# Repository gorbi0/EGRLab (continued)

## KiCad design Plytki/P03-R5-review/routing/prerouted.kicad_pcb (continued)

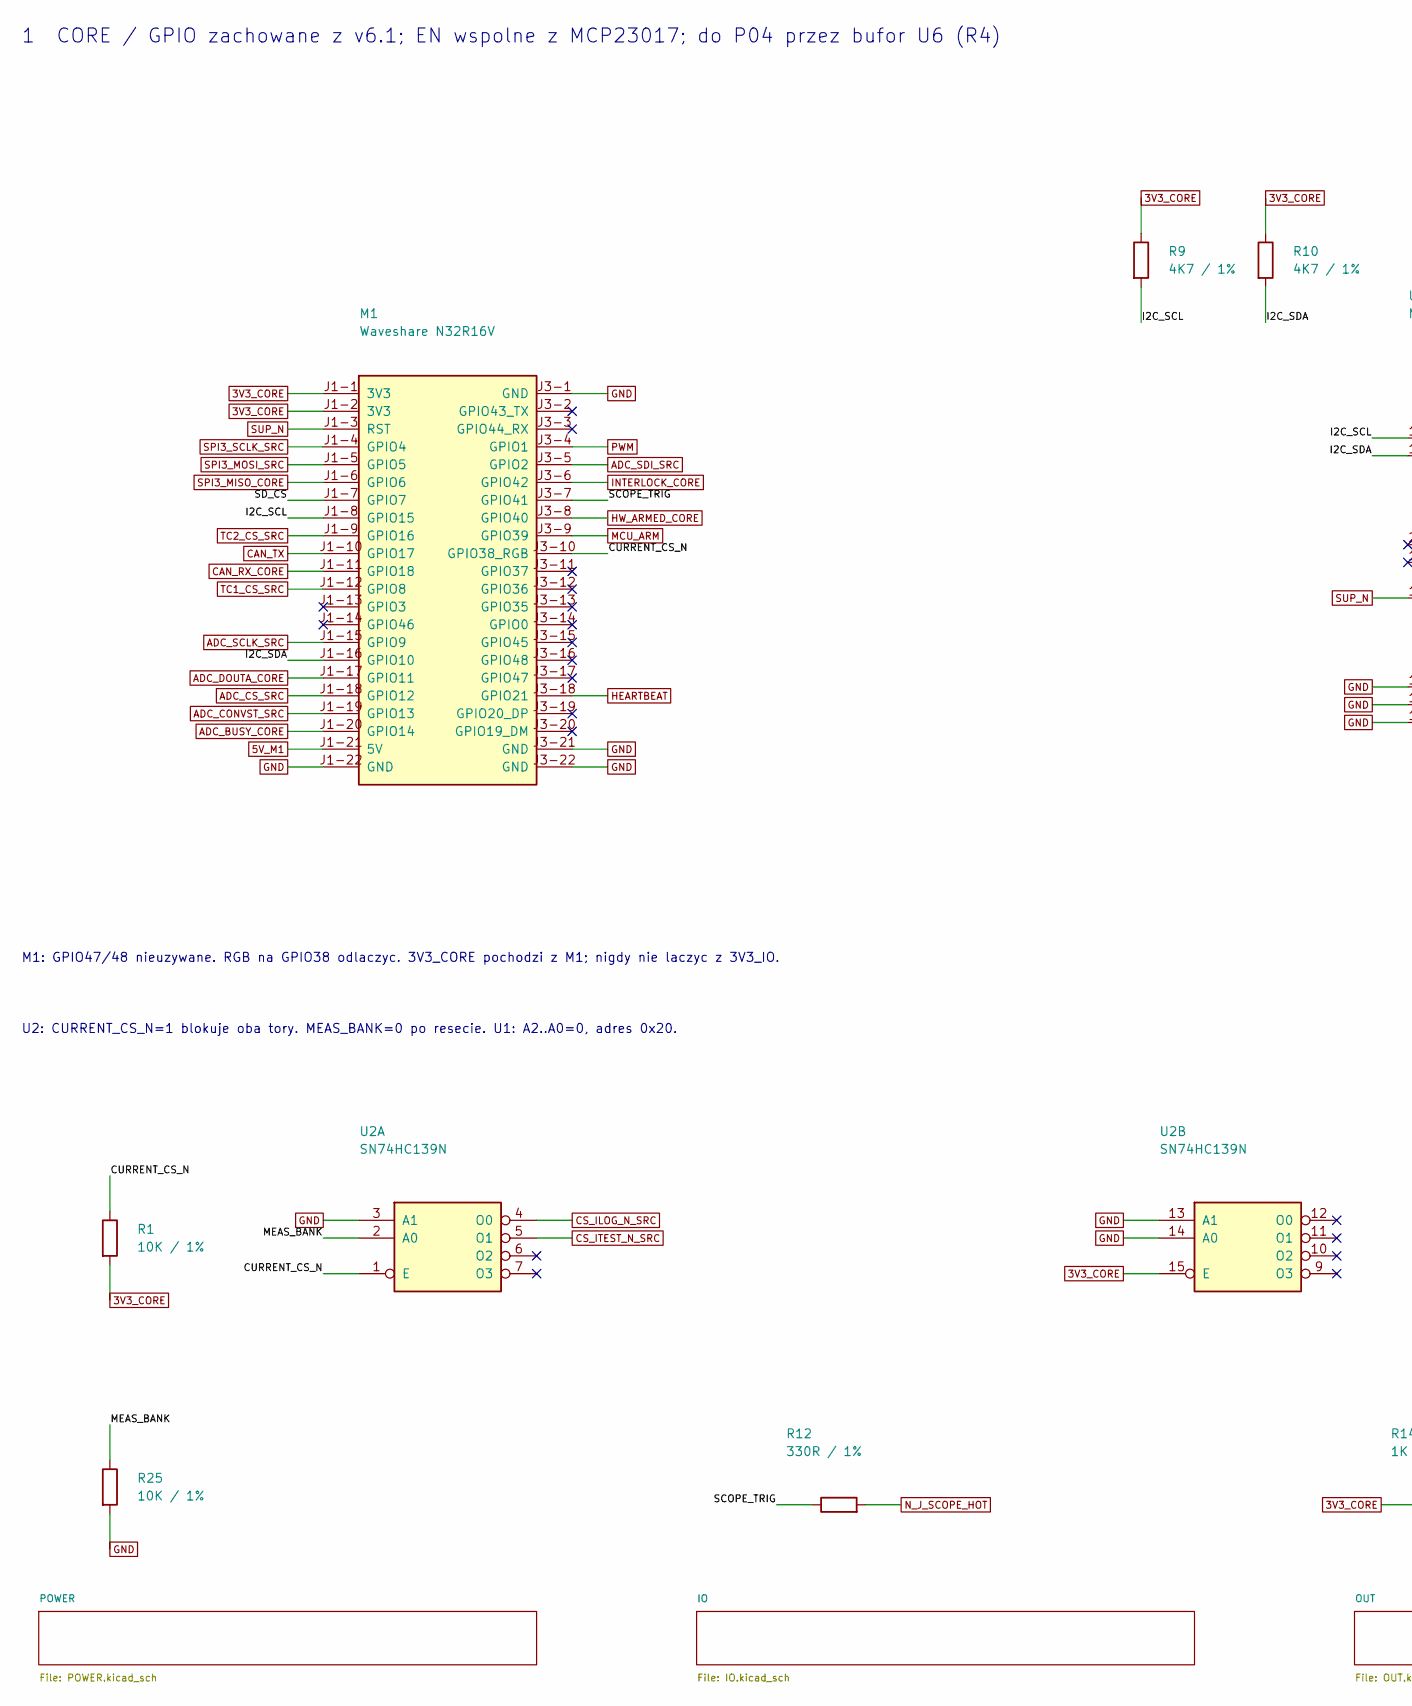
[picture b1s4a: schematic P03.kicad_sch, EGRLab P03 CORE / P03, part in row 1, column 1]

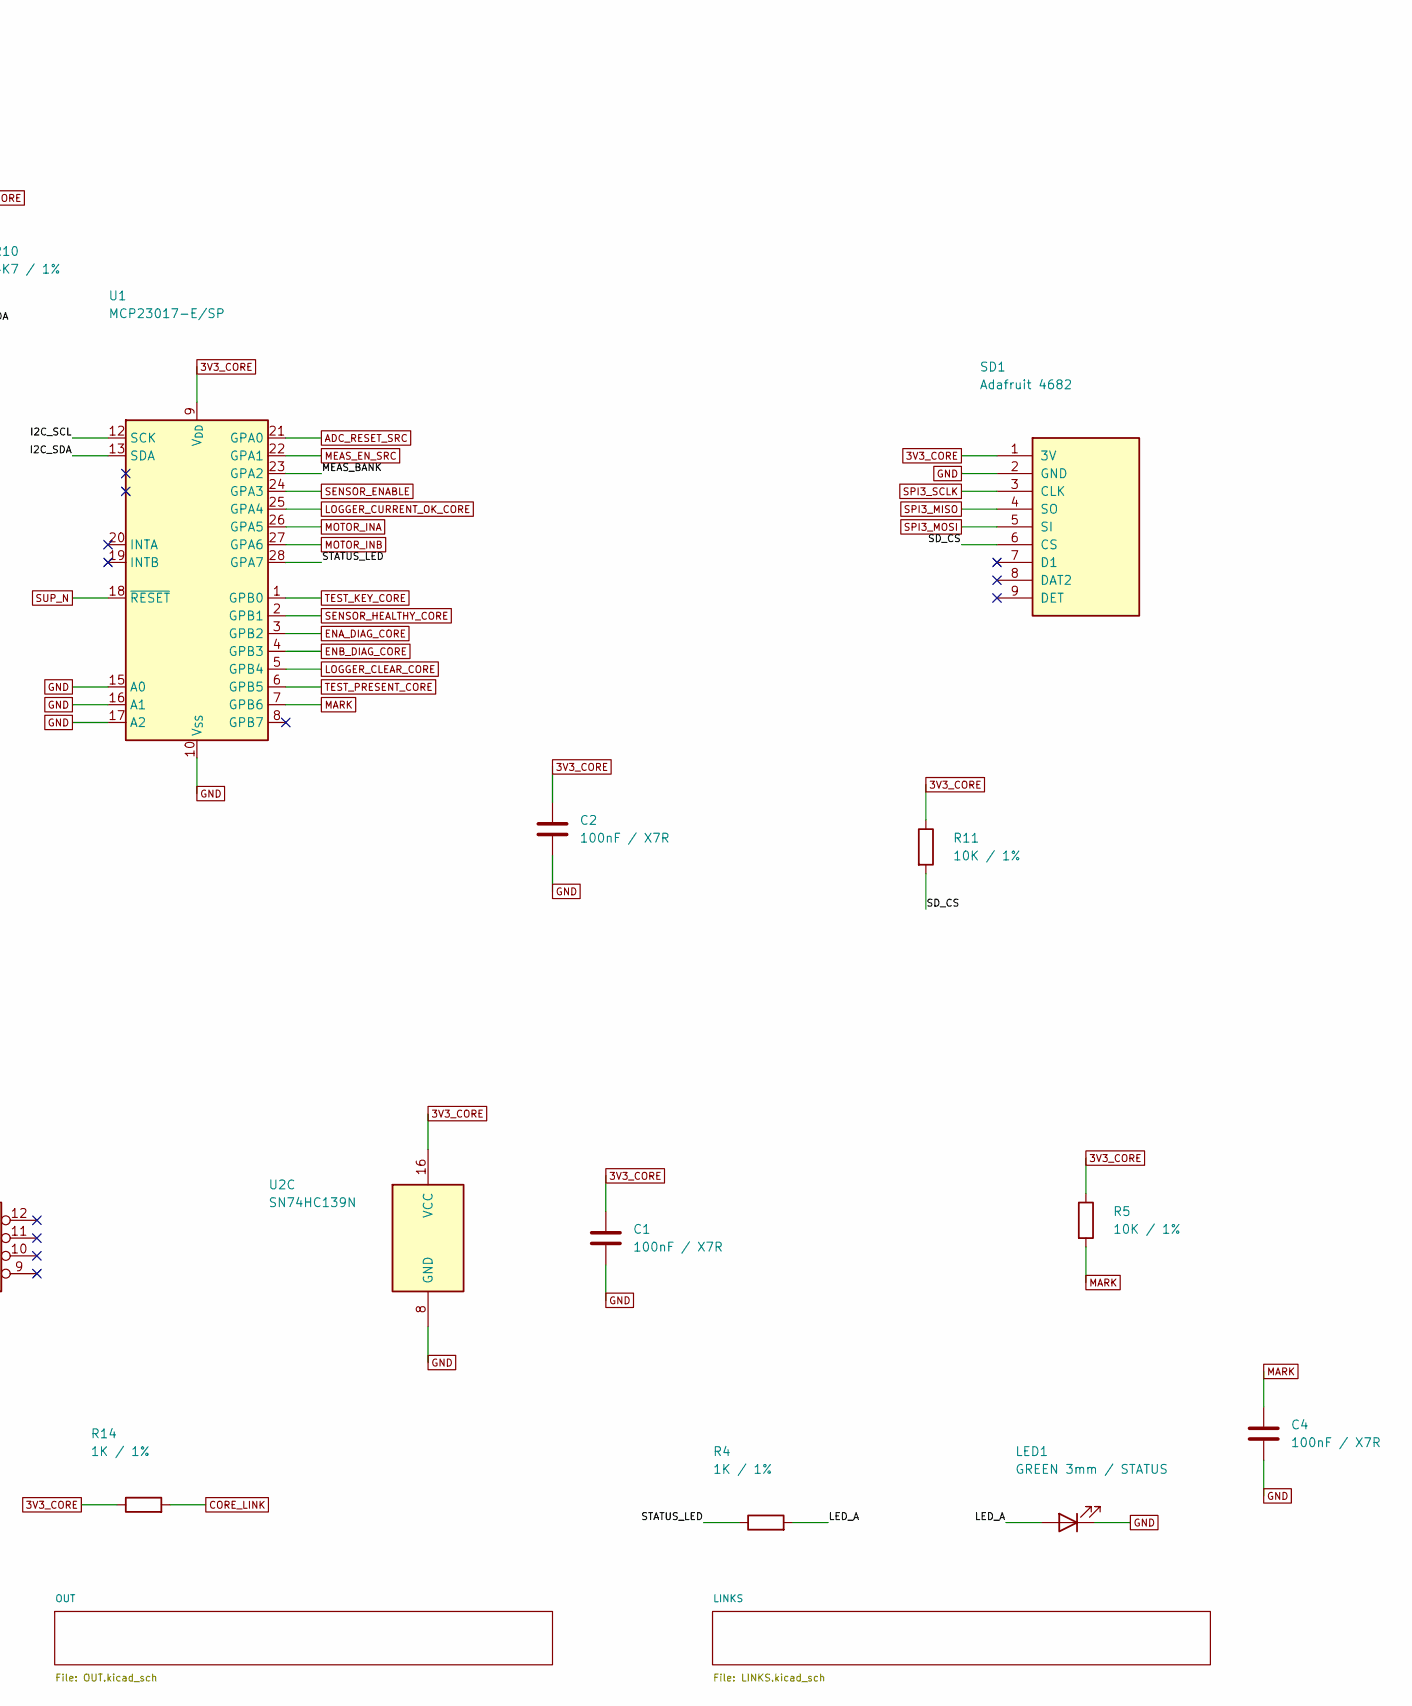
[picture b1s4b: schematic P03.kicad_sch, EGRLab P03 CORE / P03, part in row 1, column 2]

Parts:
C1, C2, C4: 100nF / X7R; C_Vishay_K15_H5_P5; MPN K104K15X7RF53H5
LED1: GREEN 3mm / STATUS; LED_D3.0mm; MPN L-934GD
M1: Waveshare N32R16V; Waveshare_ESP32-S3-DEV-KIT_2x22_W22.86; MPN owned (Waveshare ESP32-S3-DEV-KIT-N32R1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
R1, R5, R11, R25: 10K / 1%; R_Axial_DIN0207_L6.3mm_D2.5mm_P10.16mm_Horizontal; MPN MF0207FTE-10K
R4, R14: 1K / 1%; R_Axial_DIN0207_L6.3mm_D2.5mm_P10.16mm_Horizontal; MPN MF0207FTE-1K
R9, R10: 4K7 / 1%; R_Axial_DIN0207_L6.3mm_D2.5mm_P10.16mm_Horizontal; MPN MF0207FTE-4K7
R12: 330R / 1%; R_Axial_DIN0207_L6.3mm_D2.5mm_P10.16mm_Horizontal; MPN MF0207FTE-330R
SD1: Adafruit 4682; Adafruit_4682_microSD_1x09; MPN Adafruit 4682 on a 1x9 female header + 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
U1: MCP23017-E/SP; DIP-28_W7.62mm; MPN MCP23017-E/SP
U2: SN74HC139N; DIP-16_W7.62mm; MPN SN74HC139N

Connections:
3V3_CORE: C1.1, C2.1, M1.J1-1 (3V3), M1.J1-2 (3V3), R1.2, R5.1, R9.1, R10.1, R11.1, R14.1, SD1.1 (3V), U1.9 (V_{DD}), U2.15 (E), U2.16 (VCC); also elsewhere on the board
5V_M1: M1.J1-21 (5V); also elsewhere on the board
/CURRENT_CS_N: M1.J3-10 (GPIO38_RGB), R1.1, U2.1 (E)
/I2C_SCL: M1.J1-8 (GPIO15), R9.2, U1.12 (SCK)
/I2C_SDA: M1.J1-16 (GPIO10), R10.2, U1.13 (SDA)
/LED_A: LED1.2 (A), R4.2
/MEAS_BANK: R25.1, U1.23 (GPA2), U2.2 (A0)
/SCOPE_TRIG: M1.J3-7 (GPIO41), R12.1
/SD_CS: M1.J1-7 (GPIO7), R11.2, SD1.6 (CS)
/STATUS_LED: R4.1, U1.28 (GPA7)
ADC_BUSY_CORE: M1.J1-20 (GPIO14); also elsewhere on the board
ADC_CONVST_SRC: M1.J1-19 (GPIO13); also elsewhere on the board
ADC_CS_SRC: M1.J1-18 (GPIO12); also elsewhere on the board
ADC_DOUTA_CORE: M1.J1-17 (GPIO11); also elsewhere on the board
ADC_RESET_SRC: U1.21 (GPA0); also elsewhere on the board
ADC_SCLK_SRC: M1.J1-15 (GPIO9); also elsewhere on the board
ADC_SDI_SRC: M1.J3-5 (GPIO2); also elsewhere on the board
CAN_RX_CORE: M1.J1-11 (GPIO18); also elsewhere on the board
CAN_TX: M1.J1-10 (GPIO17); also elsewhere on the board
CORE_LINK: R14.2; also elsewhere on the board
CS_ILOG_N_SRC: U2.4 (O0); also elsewhere on the board
CS_ITEST_N_SRC: U2.5 (O1); also elsewhere on the board
ENA_DIAG_CORE: U1.3 (GPB2); also elsewhere on the board
ENB_DIAG_CORE: U1.4 (GPB3); also elsewhere on the board
GND: C1.2, C2.2, C4.2, LED1.1 (K), M1.J1-22 (GND), M1.J3-1 (GND), M1.J3-21 (GND), M1.J3-22 (GND), R25.2, SD1.2 (GND), U1.10 (V_{SS}), U1.15 (A0), U1.16 (A1), U1.17 (A2), U2.3 (A1), U2.8 (GND), U2.13 (A1), U2.14 (A0); also elsewhere on the board
HEARTBEAT: M1.J3-18 (GPIO21); also elsewhere on the board
HW_ARMED_CORE: M1.J3-8 (GPIO40); also elsewhere on the board
INTERLOCK_CORE: M1.J3-6 (GPIO42); also elsewhere on the board
LOGGER_CLEAR_CORE: U1.5 (GPB4); also elsewhere on the board
LOGGER_CURRENT_OK_CORE: U1.25 (GPA4); also elsewhere on the board
MARK: C4.1, R5.2, U1.7 (GPB6); also elsewhere on the board
MCU_ARM: M1.J3-9 (GPIO39); also elsewhere on the board
MEAS_EN_SRC: U1.22 (GPA1); also elsewhere on the board
MOTOR_INA: U1.26 (GPA5); also elsewhere on the board
MOTOR_INB: U1.27 (GPA6); also elsewhere on the board
N_J_SCOPE_HOT: R12.2; also elsewhere on the board
PWM: M1.J3-4 (GPIO1); also elsewhere on the board
SENSOR_ENABLE: U1.24 (GPA3); also elsewhere on the board
SENSOR_HEALTHY_CORE: U1.2 (GPB1); also elsewhere on the board
SPI3_MISO: SD1.4 (SO); also elsewhere on the board
SPI3_MISO_CORE: M1.J1-6 (GPIO6); also elsewhere on the board
SPI3_MOSI: SD1.5 (SI); also elsewhere on the board
SPI3_MOSI_SRC: M1.J1-5 (GPIO5); also elsewhere on the board
SPI3_SCLK: SD1.3 (CLK); also elsewhere on the board
SPI3_SCLK_SRC: M1.J1-4 (GPIO4); also elsewhere on the board
SUP_N: M1.J1-3 (RST), U1.18 (~RESET); also elsewhere on the board
TC1_CS_SRC: M1.J1-12 (GPIO8); also elsewhere on the board
TC2_CS_SRC: M1.J1-9 (GPIO16); also elsewhere on the board
TEST_KEY_CORE: U1.1 (GPB0); also elsewhere on the board
TEST_PRESENT_CORE: U1.6 (GPB5); also elsewhere on the board

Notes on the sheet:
1 CORE / GPIO zachowane z v6.1; EN wspolne z MCP23017; do P04 przez bufor U6 (R4)
M1: GPIO47/48 nieuzywane. RGB na GPIO38 odlaczyc. 3V3_CORE pochodzi z M1; nigdy nie laczyc z 3V3_IO.
U2: CURRENT_CS_N=1 blokuje oba tory. MEAS_BANK=0 po resecie. U1: A2..A0=0, adres 0x20.

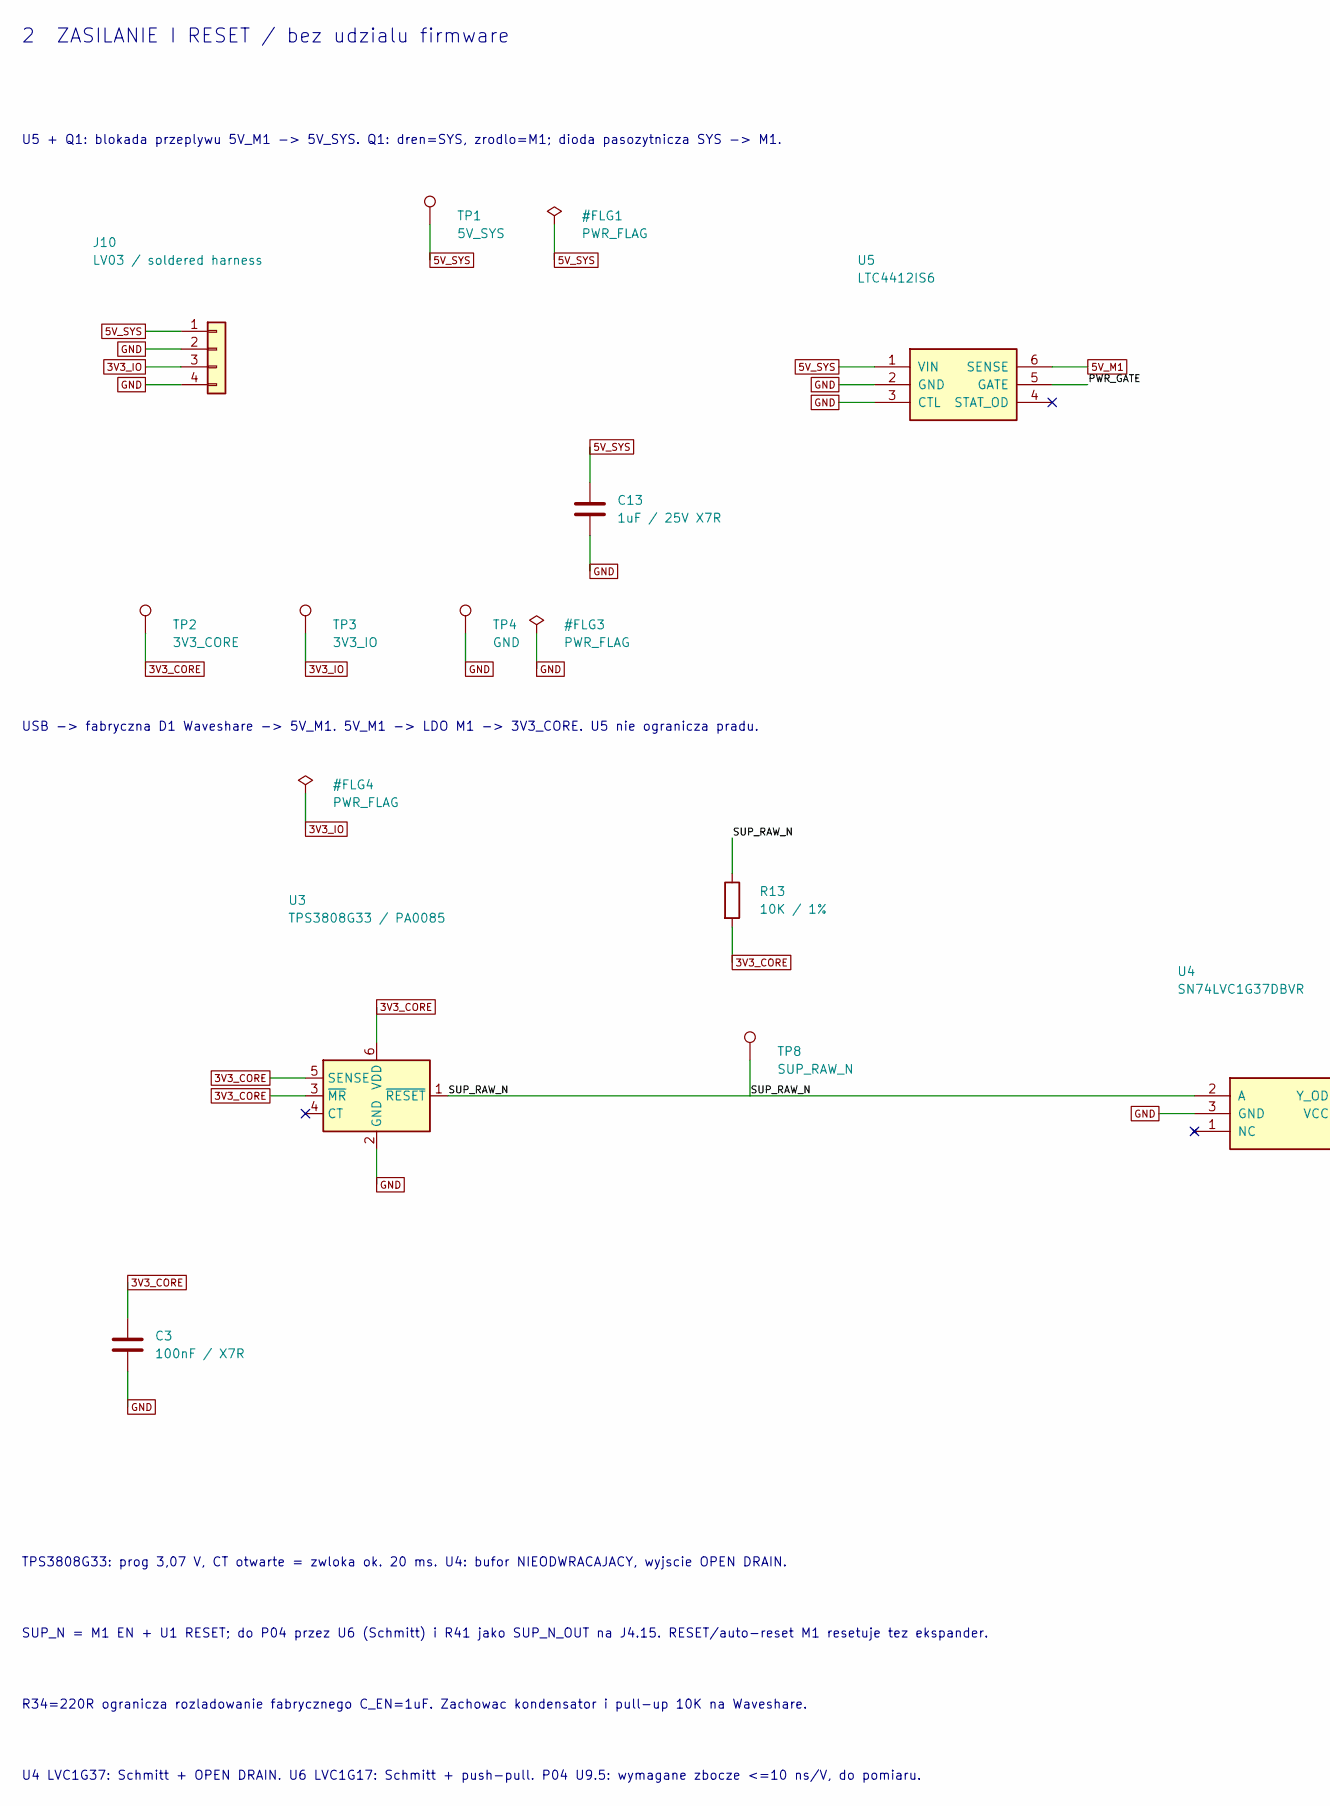
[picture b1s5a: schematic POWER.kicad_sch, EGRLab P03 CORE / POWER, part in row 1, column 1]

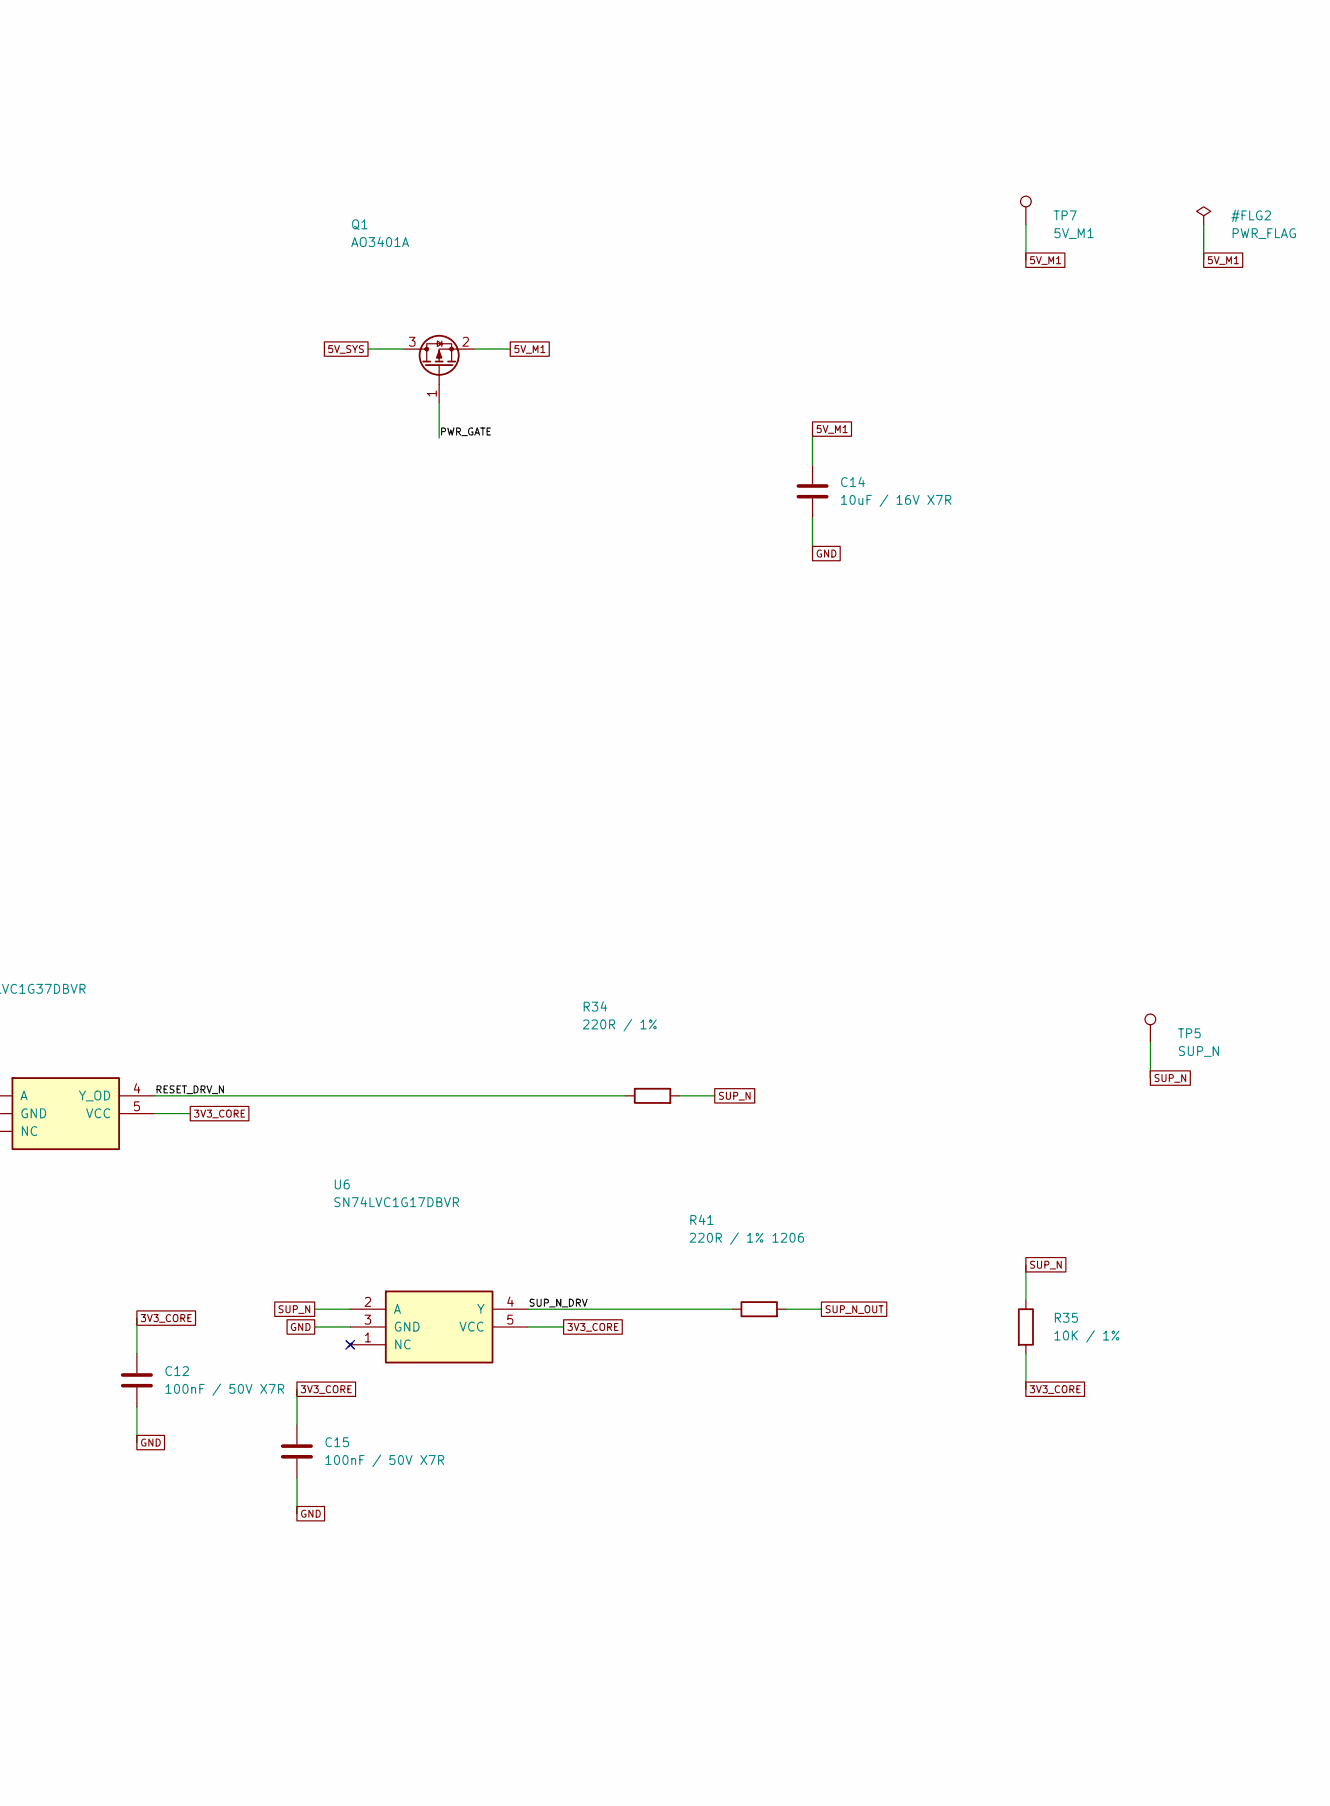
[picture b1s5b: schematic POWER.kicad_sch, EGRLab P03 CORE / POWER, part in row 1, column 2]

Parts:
C3: 100nF / X7R; C_Vishay_K15_H5_P5; MPN K104K15X7RF53H5
C12, C15: 100nF / 50V X7R; C_1206_3216Metric_Pad1.33x1.80mm_HandSolder; MPN GRM31CR71H104KA01L
C13: 1uF / 25V X7R; C_1206_3216Metric_Pad1.33x1.80mm_HandSolder; MPN GRM31CR71E105KA12L
C14: 10uF / 16V X7R; C_1206_3216Metric_Pad1.33x1.80mm_HandSolder; MPN GRM31CR71C106KA12L
J10: LV03 / soldered harness; Pigtail_LV_4xAWG22_P3.81; MPN PCB termination; H_LV03 from P02 J3
Q1: AO3401A; SOT-23; MPN AO3401A
R13, R35: 10K / 1%; R_Axial_DIN0207_L6.3mm_D2.5mm_P10.16mm_Horizontal; MPN MF0207FTE-10K
R34: 220R / 1%; R_Axial_DIN0207_L6.3mm_D2.5mm_P10.16mm_Horizontal; MPN MF0207FTE-220R
R41: 220R / 1% 1206; R_1206_3216Metric_Pad1.30x1.75mm_HandSolder; MPN RC1206FR-07220RL
TP1: 5V_SYS; TestPad_1; MPN PCB test pad
TP2: 3V3_CORE; TestPad_1; MPN PCB test pad
TP3: 3V3_IO; TestPad_1; MPN PCB test pad
TP4: GND; TestPad_1; MPN PCB test pad
TP5: SUP_N; TestPad_1; MPN PCB test pad
TP7: 5V_M1; TestPad_1; MPN PCB test pad
TP8: SUP_RAW_N; TestPad_1; MPN PCB test pad
U3: TPS3808G33 / PA0085; Adapter_SOT23-6_DIP6_W15.24_ChipQuik_PA0085; MPN TPS3808G33DBVR on Chip Quik PA0085
U4: SN74LVC1G37DBVR; SOT-23-5; MPN SN74LVC1G37DBVR
U5: LTC4412IS6; SOT-23-6; MPN LTC4412IS6#TRPBF
U6: SN74LVC1G17DBVR; SOT-23-5; MPN SN74LVC1G17DBVR

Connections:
3V3_CORE: C3.1, C12.1, C15.1, R13.2, R35.2, TP2.1, U3.3 (~MR), U3.5 (SENSE), U3.6 (VDD), U4.5 (VCC), U6.5 (VCC); also elsewhere on the board
3V3_IO: J10.3, TP3.1; also elsewhere on the board
5V_M1: C14.1, Q1.2 (S), TP7.1, U5.6 (SENSE); also elsewhere on the board
5V_SYS: C13.1, J10.1, Q1.3 (D), TP1.1, U5.1 (VIN)
/POWER/PWR_GATE: Q1.1 (G), U5.5 (GATE)
/POWER/RESET_DRV_N: R34.1, U4.4 (Y_OD)
/POWER/SUP_N_DRV: R41.1, U6.4 (Y)
/POWER/SUP_RAW_N: R13.1, TP8.1, U3.1 (~RESET), U4.2 (A)
GND: C3.2, C12.2, C13.2, C14.2, C15.2, J10.2, J10.4, TP4.1, U3.2 (GND), U4.3 (GND), U5.2 (GND), U5.3 (CTL), U6.3 (GND); also elsewhere on the board
SUP_N: R34.2, R35.1, TP5.1, U6.2 (A); also elsewhere on the board
SUP_N_OUT: R41.2; also elsewhere on the board

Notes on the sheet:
2 ZASILANIE I RESET / bez udzialu firmware
U5 + Q1: blokada przeplywu 5V_M1 -> 5V_SYS. Q1: dren=SYS, zrodlo=M1; dioda pasozytnicza SYS -> M1.
USB -> fabryczna D1 Waveshare -> 5V_M1. 5V_M1 -> LDO M1 -> 3V3_CORE. U5 nie ogranicza pradu.
TPS3808G33: prog 3,07 V, CT otwarte = zwloka ok. 20 ms. U4: bufor NIEODWRACAJACY, wyjscie OPEN DRAIN.
SUP_N = M1 EN + U1 RESET; do P04 przez U6 (Schmitt) i R41 jako SUP_N_OUT na J4.15. RESET/auto-reset M1 resetuje tez ekspander.
R34=220R ogranicza rozladowanie fabrycznego C_EN=1uF. Zachowac kondensator i pull-up 10K na Waveshare.
U4 LVC1G37: Schmitt + OPEN DRAIN. U6 LVC1G17: Schmitt + push-pull. P04 U9.5: wymagane zbocze <=10 ns/V, do pomiaru.

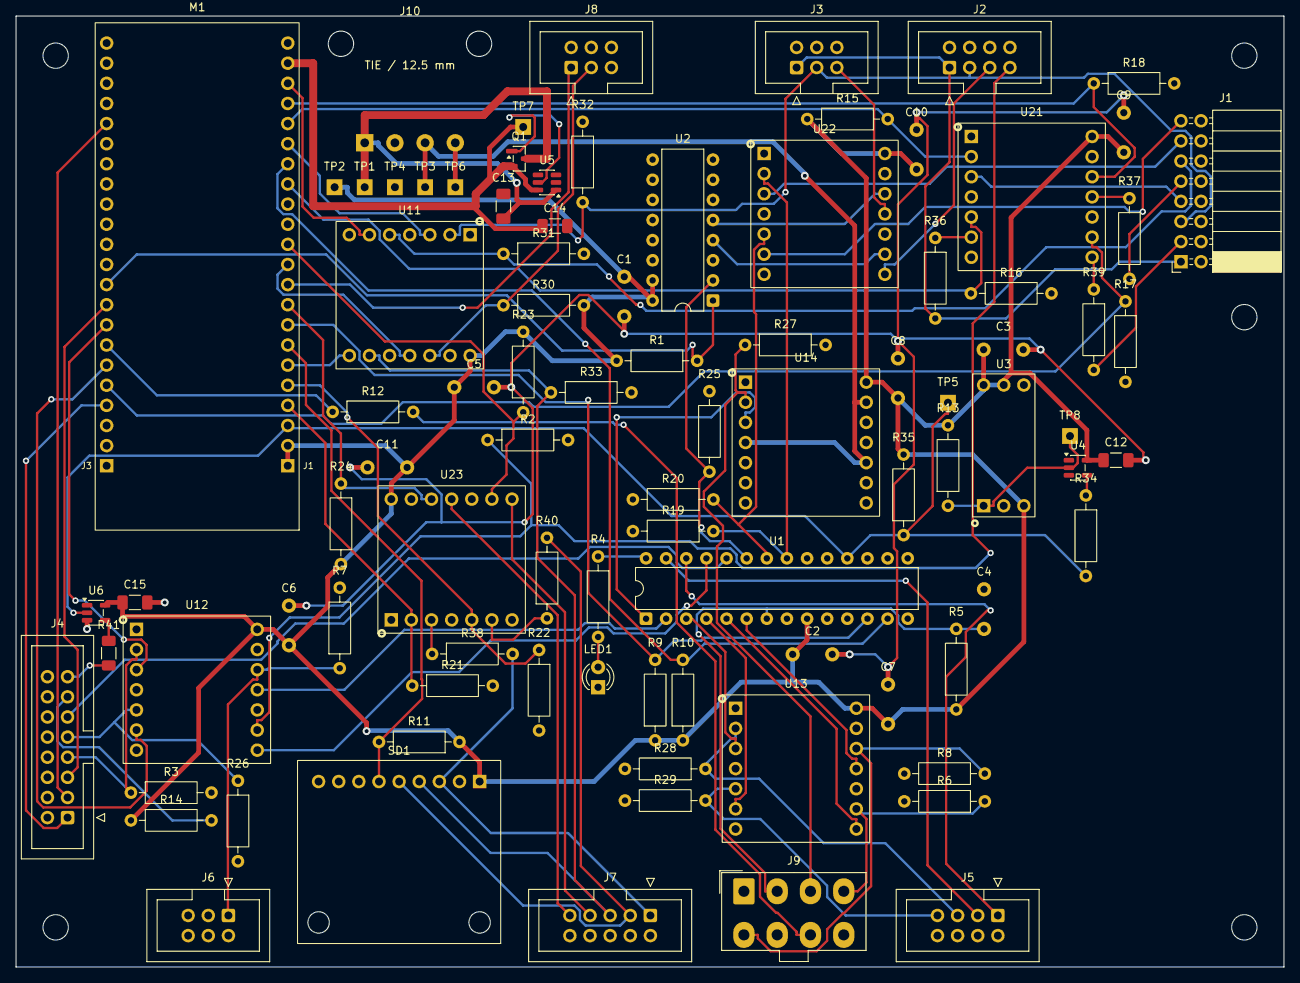
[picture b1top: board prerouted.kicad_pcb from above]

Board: 2 copper layers, 160.0 x 120.0 mm, 96 parts (0 on the bottom side), 84 nets.

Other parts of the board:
H1, H2, H3, H4, H5: M3 NPTH

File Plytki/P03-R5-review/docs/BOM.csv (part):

ref;source_ref;display;mpn;qty;footprint;url;note
M1;M1;Waveshare N32R16V;owned (Waveshare ESP32-S3-DEV-KIT-N32R16V) on 2x 1x22 female headers;1;P03:Waveshare_ESP32-S3-DEV-KIT_2x22_W22.86;https://docs.waveshare.com/ESP32-S3-DEV-KIT-N8R8;"Rows 22.86 mm (measured). GPIO numbers are the v6.1 contract. Remove the on-board RGB LED on GPIO38 (v6.1). GPIO47/48 1.8 V: unused. 3V3 = 3V3_CORE; never tie to 3V3_IO."
SD1;SD1;Adafruit 4682;Adafruit 4682 on a 1x9 female header + 2x M2.5 spacer;1;P03:Adafruit_4682_microSD_1x09;https://www.adafruit.com/product/4682;User decision 25.09: Adafruit 4682 (3 V only, no regulator/level shifter). SO = card out (MISO), SI = card in (MOSI). D1, DAT2, DET unused.
U1;U17;MCP23017-E/SP;MCP23017-E/SP;1;Package_DIP:DIP-28_W7.62mm;https://ww1.microchip.com/downloads/en/devicedoc/20001952c.pdf;Address 0x20 (A2..A0 = GND). IODIRA 0x10, IODIRB 0x7F (v6.1). In 2x DIP14 precision sockets end to end (bought).
C2;C_DEC_U17_9;100nF / X7R;K104K15X7RF53H5;1;P03:C_Vishay_K15_H5_P5;https://www.vishay.com/docs/45171/kseries.pdf;At U1 pin 9.
U2;U_CS;SN74HC139N;SN74HC139N;1;Package_DIP:DIP-16_W7.62mm;https://www.ti.com/lit/ds/symlink/sn74hc139.pdf;/G = GPIO38, A = MEAS_BANK, B = GND (v6.1). Second half disabled. DIP16 socket (bought).
C1;C_CS;100nF / X7R;K104K15X7RF53H5;1;P03:C_Vishay_K15_H5_P5;https://www.vishay.com/docs/45171/kseries.pdf;At U2 pin 16.
R1;R_CS_IDLE;10K / 1%;MF0207FTE-10K;1;Resistor_THT:R_Axial_DIN0207_L6.3mm_D2.5mm_P10.16mm_Horizontal;https://www.yageo.com/upload/media/product/productsearch/dat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;Decoder disabled while GPIO38 floats.
U3;U5;TPS3808G33 / PA0085;TPS3808G33DBVR on Chip Quik PA0085;1;P03:Adapter_SOT23-6_DIP6_W15.24_ChipQuik_PA0085;https://www.ti.com/lit/ds/symlink/tps3808.pdf;SOT23-6 on PA0085 (rows 15.24 mm, measured). Pin n = SOT pin n: confirm on the adapter before soldering. CT open = fixed delay.
C3;C_DEC_U5_6;100nF / X7R;K104K15X7RF53H5;1;P03:C_Vishay_K15_H5_P5;https://www.vishay.com/docs/45171/kseries.pdf;At U3 pin 6.
R13;R_SUP_PU;10K / 1%;MF0207FTE-10K;1;Resistor_THT:R_Axial_DIN0207_L6.3mm_D2.5mm_P10.16mm_Horizontal;https://www.yageo.com/upload/media/product/productsearch/dat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;"Supervisor pull-up before U4; does not discharge Waveshare EN capacitor."
R9;R_PU_I2C_SCL;4K7 / 1%;MF0207FTE-4K7;1;Resistor_THT:R_Axial_DIN0207_L6.3mm_D2.5mm_P10.16mm_Horizontal;https://www.yageo.com/upload/media/product/productsearch/dat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;
R10;R_PU_I2C_SDA;4K7 / 1%;MF0207FTE-4K7;1;Resistor_THT:R_Axial_DIN0207_L6.3mm_D2.5mm_P10.16mm_Horizontal;https://www.yageo.com/upload/media/product/productsearch/dat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;
R11;R_PU_SD_CS;10K / 1%;MF0207FTE-10K;1;Resistor_THT:R_Axial_DIN0207_L6.3mm_D2.5mm_P10.16mm_Horizontal;https://www.yageo.com/upload/media/product/productsearch/dat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;Card deselected while GPIO7 floats.
R12;R_SCOPE;330R / 1%;MF0207FTE-330R;1;Resistor_THT:R_Axial_DIN0207_L6.3mm_D2.5mm_P10.16mm_Horizontal;https://www.yageo.com/upload/media/product/productsearch/dat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;SCOPE_TRIG series resistor to PANELCORE pin 7.
R5;R_MARK;10K / 1%;MF0207FTE-10K;1;Resistor_THT:R_Axial_DIN0207_L6.3mm_D2.5mm_P10.16mm_Horizontal;https://www.yageo.com/upload/media/product/productsearch/dat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;
C4;C_MARK;100nF / X7R;K104K15X7RF53H5;1;P03:C_Vishay_K15_H5_P5;https://www.vishay.com/docs/45171/kseries.pdf;MARK button debounce.
R4;R_LED;1K / 1%;MF0207FTE-1K;1;Resistor_THT:R_Axial_DIN0207_L6.3mm_D2.5mm_P10.16mm_Horizontal;https://www.yageo.com/upload/media/product/productsearch/dat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;
LED1;LED1;GREEN 3mm / STATUS;L-934GD;1;LED_THT:LED_D3.0mm;https://www.kingbrightusa.com/images/catalog/SPEC/L-934GD.pdf;MCP23017 GPA7.
R14;W_LINK;1K / 1%;MF0207FTE-1K;1;Resistor_THT:R_Axial_DIN0207_L6.3mm_D2.5mm_P10.16mm_Horizontal;https://www.yageo.com/upload/media/product/productsearch/dat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;"CORE_LINK = presence of 3V3_CORE through 1 k (R3, review P3-02): a harness short to GND draws 3.3 mA; P04 R16 10 k sees >= 2.85 V (74LVC125A VIH 2.0 V). v6.1 had a wire link."
J10;J_LV03B;LV03 / soldered harness;"PCB termination; H_LV03 from P02 J3";1;P03:Pigtail_LV_4xAWG22_P3.81;;H_LV03: 4 x AWG22, 200 mm, Mini-Fit Jr 4p at P02 (LV03). Soldered here, anchor 12.5 mm (v6.1: soldered end on P03).
U11;U_IN1;74LVC125A;74LVC125AD,118 (Nexperia) on Kamami 575068;1;P03:Adapter_SO14_DIP14_W15.24_Kamami575068;https://assets.nexperia.com/documents/data-sheet/74LVC125A.pdf;Nexperia only (Ioff), v6.1.
C5;C_U_IN1;100nF / X7R;K104K15X7RF53H5;1;P03:C_Vishay_K15_H5_P5;https://www.vishay.com/docs/45171/kseries.pdf;At U11 pin 14.
U12;U_IN2;74LVC125A;74LVC125AD,118 (Nexperia) on Kamami 575068;1;P03:Adapter_SO14_DIP14_W15.24_Kamami575068;https://assets.nexperia.com/documents/data-sheet/74LVC125A.pdf;Nexperia only (Ioff), v6.1.
C6;C_U_IN2;100nF / X7R;K104K15X7RF53H5;1;P03:C_Vishay_K15_H5_P5;https://www.vishay.com/docs/45171/kseries.pdf;At U12 pin 14.
U13;U_IN3;74LVC125A;74LVC125AD,118 (Nexperia) on Kamami 575068;1;P03:Adapter_SO14_DIP14_W15.24_Kamami575068;https://assets.nexperia.com/documents/data-sheet/74LVC125A.pdf;Nexperia only (Ioff), v6.1.
C7;C_U_IN3;100nF / X7R;K104K15X7RF53H5;1;P03:C_Vishay_K15_H5_P5;https://www.vishay.com/docs/45171/kseries.pdf;At U13 pin 14.
U14;U_IN4;74LVC125A;74LVC125AD,118 (Nexperia) on Kamami 575068;1;P03:Adapter_SO14_DIP14_W15.24_Kamami575068;https://assets.nexperia.com/documents/data-sheet/74LVC125A.pdf;Nexperia only (Ioff), v6.1. Unused OE# = 3V3_IO in U_IN4 as in v6.1.
C8;C_U_IN4;100nF / X7R;K104K15X7RF53H5;1;P03:C_Vishay_K15_H5_P5;https://www.vishay.com/docs/45171/kseries.pdf;At U14 pin 14.
U21;U_OUT1;74LVC125A;74LVC125AD,118 (Nexperia) on Kamami 575068;1;P03:Adapter_SO14_DIP14_W15.24_Kamami575068;https://assets.nexperia.com/documents/data-sheet/74LVC125A.pdf;Nexperia only (Ioff), v6.1.
C9;C_U_OUT1;100nF / X7R;K104K15X7RF53H5;1;P03:C_Vishay_K15_H5_P5;https://www.vishay.com/docs/45171/kseries.pdf;At U21 pin 14.
U22;U_OUT2;74LVC125A;74LVC125AD,118 (Nexperia) on Kamami 575068;1;P03:Adapter_SO14_DIP14_W15.24_Kamami575068;https://assets.nexperia.com/documents/data-sheet/74LVC125A.pdf;Nexperia only (Ioff), v6.1.
C10;C_U_OUT2;100nF / X7R;K104K15X7RF53H5;1;P03:C_Vishay_K15_H5_P5;https://www.vishay.com/docs/45171/kseries.pdf;At U22 pin 14.
U23;U_OUT3;74LVC125A;74LVC125AD,118 (Nexperia) on Kamami 575068;1;P03:Adapter_SO14_DIP14_W15.24_Kamami575068;https://assets.nexperia.com/documents/data-sheet/74LVC125A.pdf;Nexperia only (Ioff), v6.1.
C11;C_U_OUT3;100nF / X7R;K104K15X7RF53H5;1;P03:C_Vishay_K15_H5_P5;https://www.vishay.com/docs/45171/kseries.pdf;At U23 pin 14.
R2;R_CURRENT_OK;10K / 1%;MF0207FTE-10K;1;Resistor_THT:R_Axial_DIN0207_L6.3mm_D2.5mm_P10.16mm_Horizontal;https://www.yageo.com/upload/media/product/productsearch/dat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;Receiver pull-down: open cable = not OK.
R3;R_HW_PD;10K / 1%;MF0207FTE-10K;1;Resistor_THT:R_Axial_DIN0207_L6.3mm_D2.5mm_P10.16mm_Horizontal;https://www.yageo.com/upload/media/product/productsearch/dat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;Receiver pull-down.
R6;R_PD_LOGGER_CLEAR;10K / 1%;MF0207FTE-10K;1;Resistor_THT:R_Axial_DIN0207_L6.3mm_D2.5mm_P10.16mm_Horizontal;https://www.yageo.com/upload/media/product/productsearch/dat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;Receiver pull-down.
R7;R_PD_SENSOR_HEALTHY;10K / 1%;MF0207FTE-10K;1;Resistor_THT:R_Axial_DIN0207_L6.3mm_D2.5mm_P10.16mm_Horizontal;https://www.yageo.com/upload/media/product/productsearch/dat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;Receiver pull-down: cable open or transmitter unpowered = fault (v6.1).
R8;R_PD_TEST_PRESENT;10K / 1%;MF0207FTE-10K;1;Resistor_THT:R_Axial_DIN0207_L6.3mm_D2.5mm_P10.16mm_Horizontal;https://www.yageo.com/upload/media/product/productsearch/dat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;Receiver pull-down.
J1;J_DAQA;DAQ B2B / RA socket 2x8;Samtec SSW-108-02-G-D-RA (right-angle 2x8 socket, Au) or equivalent;1;Connector_PinSocket_2.54mm:PinSocket_2x08_P2.54mm_Horizontal;https://www.samtec.com/products/ssw;User decision 25.09: P05 beside P03, right-angle pair edge to edge. Key: position 2 blocked here, pin 2 removed on P05 (v6.1).
J2;J_ILOGA;ILOG / IDC 2x4 KEY 2;IDC box header 2x4, 2.54 mm, Au;1;Connector_IDC:IDC-Header_2x04_P2.54mm_Vertical;;KEY 2: remove header pin 2 (v6.1).
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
